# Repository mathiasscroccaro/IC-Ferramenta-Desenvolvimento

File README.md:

# IC Ferramenta Desenvolvimento 2017/01
Esquemáticos, códigos fonte e interface LabView desenvolvidos durante IC

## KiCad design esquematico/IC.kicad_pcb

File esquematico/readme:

Os esquemáticos podem ser visualizados com o software EDA Kicad

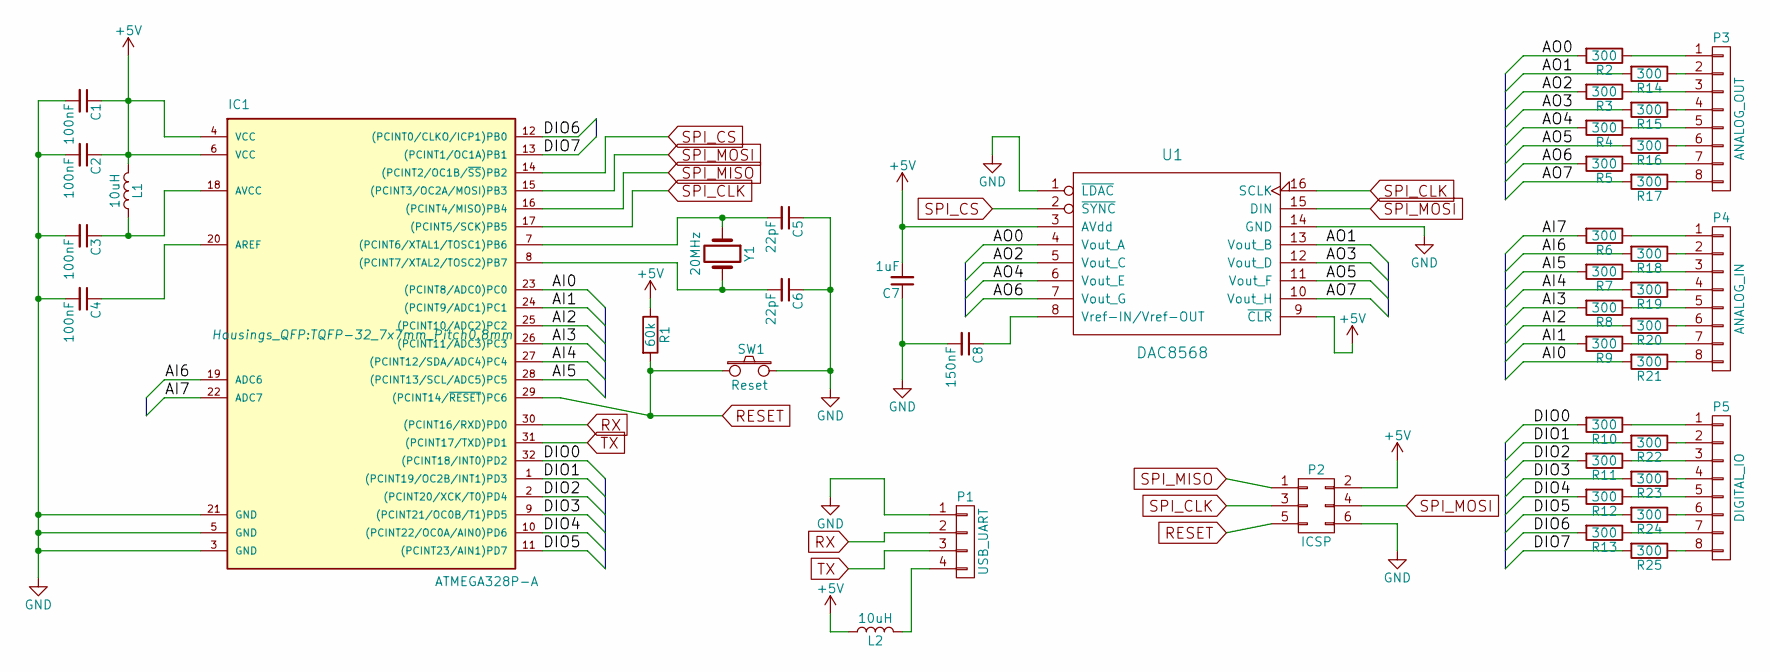
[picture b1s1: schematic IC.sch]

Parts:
C1, C2, C3, C4: 100nF; C_1206_HandSoldering
C5, C6: 22pF; C_1206_HandSoldering
C7: 1uF; C_1206_HandSoldering
C8: 150nF; C_1206_HandSoldering
IC1: ATMEGA328P-A; TQFP-32_7x7mm_Pitch0.8mm
L1, L2: 10uH; Choke_SMD_1206_Standard
P1: USB_UART; Pin_Header_Angled_1x04_Pitch2.54mm
P2: ICSP; Pin_Header_Straight_2x03_Pitch2.54mm
P3: ANALOG_OUT; Pin_Header_Straight_1x08_Pitch2.54mm
P4: ANALOG_IN; Pin_Header_Straight_1x08_Pitch2.54mm
P5: DIGITAL_IO; Pin_Header_Straight_1x08_Pitch2.54mm
R1: 60k; R_1206_HandSoldering
R2, R3, R4, R5, R6, R7, R8, R9, R10, R11, R12, R13, R14, R15, R16, R17, R18, R19, R20, R21, R22, R23, R24, R25: 300; R_1206_HandSoldering
SW1: Reset; SW_SPST_FSMSM
U1: DAC8568; SSOP-16_5.3x6.2mm_Pitch0.65mm
Y1: 20MHz; Crystal_HC18-U_Vertical

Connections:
+5V: C1.1, C2.1, C7.2, IC1.4 (VCC), IC1.6 (VCC), L1.2, L2.1, P2.2, R1.1, U1.3 (AVdd), U1.9 (~CLR)
/AI0: IC1.23 ((PCINT8/ADC0)PC0), R21.2
/AI1: IC1.24 ((PCINT9/ADC1)PC1), R9.2
/AI2: IC1.25 ((PCINT10/ADC2)PC2), R20.2
/AI3: IC1.26 ((PCINT11/ADC3)PC3), R8.2
/AI4: IC1.27 ((PCINT12/SDA/ADC4)PC4), R19.2
/AI5: IC1.28 ((PCINT13/SCL/ADC5)PC5), R7.2
/AI6: IC1.19 (ADC6), R18.2
/AI7: IC1.22 (ADC7), R6.2
/AO0: R2.2, U1.4 (Vout_A)
/AO1: R14.2, U1.13 (Vout_B)
/AO2: R3.2, U1.5 (Vout_C)
/AO3: R15.2, U1.12 (Vout_D)
/AO4: R4.2, U1.6 (Vout_E)
/AO5: R16.2, U1.11 (Vout_F)
/AO6: R5.2, U1.7 (Vout_G)
/AO7: R17.2, U1.10 (Vout_H)
/DIO0: IC1.32 ((PCINT18/INT0)PD2), R10.2
/DIO1: IC1.1 ((PCINT19/OC2B/INT1)PD3), R22.2
/DIO2: IC1.2 ((PCINT20/XCK/T0)PD4), R11.2
/DIO3: IC1.9 ((PCINT21/OC0B/T1)PD5), R23.2
/DIO4: IC1.10 ((PCINT22/OC0A/AIN0)PD6), R12.2
/DIO5: IC1.11 ((PCINT23/AIN1)PD7), R24.2
/DIO6: IC1.12 ((PCINT0/CLKO/ICP1)PB0), R13.2
/DIO7: IC1.13 ((PCINT1/OC1A)PB1), R25.2
GND: C1.2, C2.2, C3.2, C4.2, C5.1, C6.1, C7.1, C8.2, IC1.3 (GND), IC1.5 (GND), IC1.21 (GND), P1.1, P2.6, SW1.2, U1.1 (~LDAC), U1.14 (GND)
unnamed: C3.1, IC1.18 (AVCC), L1.1
unnamed: C4.1, IC1.20 (AREF)
unnamed: C5.2, IC1.7 ((PCINT6/XTAL1/TOSC1)PB6), Y1.1
unnamed: C6.2, IC1.8 ((PCINT7/XTAL2/TOSC2)PB7), Y1.2
unnamed: C8.1, U1.8 (Vref-IN/Vref-OUT)
unnamed: L2.2, P1.4
unnamed: P3.1, R2.1
unnamed: P3.2, R14.1
unnamed: P3.3, R3.1
unnamed: P3.4, R15.1
unnamed: P3.5, R4.1
unnamed: P3.6, R16.1
unnamed: P3.7, R5.1
unnamed: P3.8, R17.1
unnamed: P4.1, R6.1
unnamed: P4.2, R18.1
unnamed: P4.3, R7.1
unnamed: P4.4, R19.1
unnamed: P4.5, R8.1
unnamed: P4.6, R20.1
unnamed: P4.7, R9.1
unnamed: P4.8, R21.1
unnamed: P5.1, R10.1
unnamed: P5.2, R22.1
unnamed: P5.3, R11.1
unnamed: P5.4, R23.1
unnamed: P5.5, R12.1
unnamed: P5.6, R24.1
unnamed: P5.7, R13.1
unnamed: P5.8, R25.1
RESET: IC1.29 ((PCINT14/~RESET~)PC6), P2.5, R1.2, SW1.1
RX: IC1.30 ((PCINT16/RXD)PD0), P1.2
SPI_CLK: IC1.17 ((PCINT5/SCK)PB5), P2.3, U1.16 (SCLK)
SPI_CS: IC1.14 ((PCINT2/OC1B/~SS~)PB2), U1.2 (~SYNC)
SPI_MISO: IC1.16 ((PCINT4/MISO)PB4), P2.1
SPI_MOSI: IC1.15 ((PCINT3/OC2A/MOSI)PB3), P2.4, U1.15 (DIN)
TX: IC1.31 ((PCINT17/TXD)PD1), P1.3

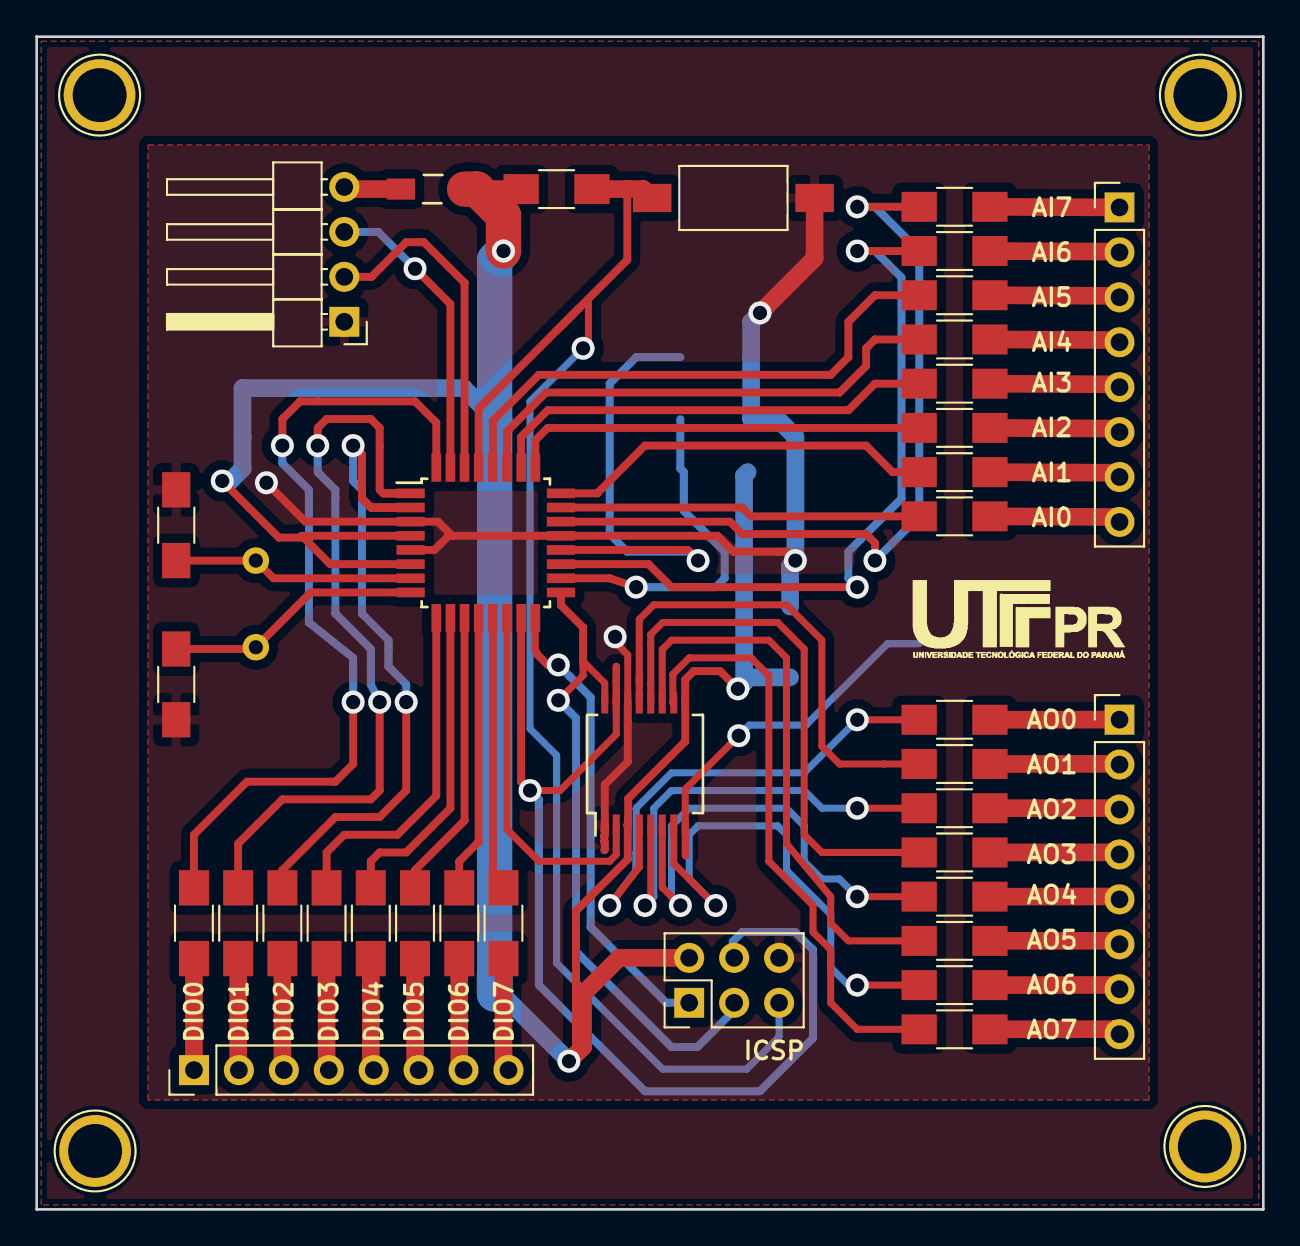
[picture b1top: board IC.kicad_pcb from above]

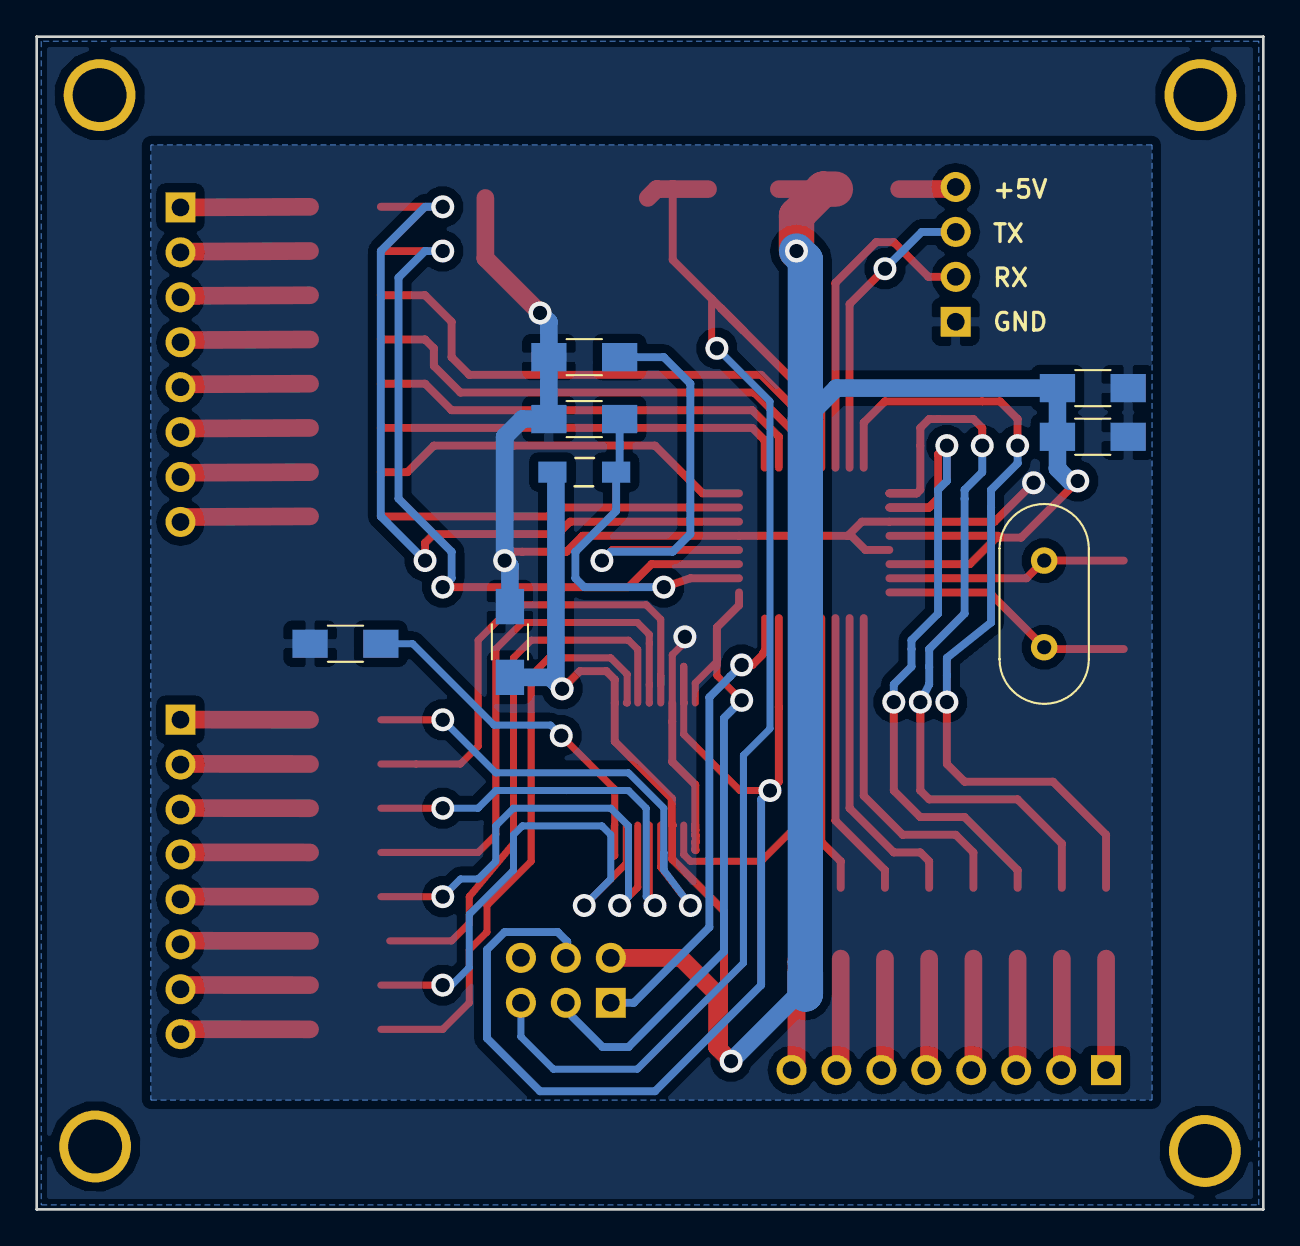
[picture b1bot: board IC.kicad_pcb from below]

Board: 2 copper layers, 69.3 x 66.3 mm, 45 parts (8 on the bottom side), 63 nets.

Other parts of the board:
LOGO: LOGO

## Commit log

2017-07-04 Create gerber_drill
